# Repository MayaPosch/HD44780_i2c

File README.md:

# HD44780-compatible I2C adapter #

This project is an I2C expander module based around a Texas Instruments TCA6416A I2C GPIO expander. It allows for interfacing with a variety of 14 to 16-pin, HD44780-compatible displays:

- 14-pin without backlight.
- 16-pin with A/K backlight pins after pin 14.
- 16-pin with A/K backlight pins before pin 1.
- 16-pin with Vee negative bias voltage output on pin 16 instead of backlight ground.

This adapter is compatible with both 3.3V and 5V I2C bus levels. The 5-pin MCU/MPU side header has the following connections:

1. **Vlcd:** LCD-side voltage. This is 5V for a 5V display.
2. **GND:** Ground connection.
3. **VDD:** I2C bus voltage. This is 3.3V for a 3.3V MCU.
4. **SDA:** I2C data line. At MCU level voltage.
5. **SCL:** I2C clock line. At MCU level voltage.

## I2C address ##

Default I2C 7-bit address is 0x20, set with JP1 (1-2 connected). To use the alternate 0x21 address, cut the connection on JP1 between pads 1 & 2, and connect 2-3.

## GPIO header ##

Four GPIO pins from the I2C expander are broken out into a 5-pin header (J3). These can be freely used, limited by the TCA6416A's capabilities.

## Vlcd-Vee backlight ##

When a display is connected that does not use pin 16 for Vee (negative bias), but instead expects a 5V backlight supply voltage on this, connect the `Vlcd-Vee` connector with a jumper.

## Backlight enable ##

The backlight on/off state is controlled by GPIO 0 of the TCA6416A via Q1.

## Contrast adjustment ##

For contrast adjustment, a potentiometer on the board is provided.

## TODO ##

This is currently a prototype design. It's likely that some things may not fully work as intended yet.

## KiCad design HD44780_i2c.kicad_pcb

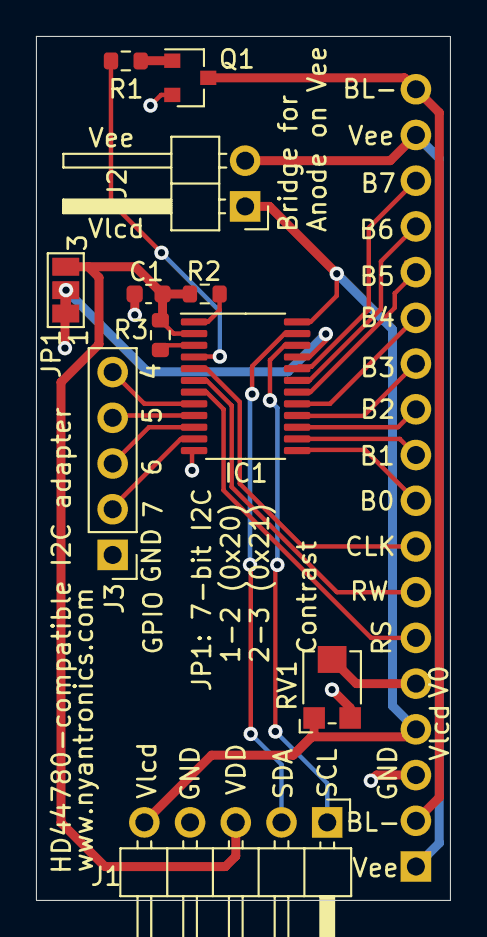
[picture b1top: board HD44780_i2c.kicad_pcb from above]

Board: 2 copper layers, 23.0 x 48.0 mm, 12 parts (1 on the bottom side), 28 nets.

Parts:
C1: 100nF; C_0603_1608Metric
IC1: TCA6416APWR; TSSOP-24_4.4x7.8mm_P0.65mm
J1: Conn_01x05_Male; PinHeader_1x05_P2.54mm_Horizontal
J2: Conn_01x02_Male; PinHeader_1x02_P2.54mm_Horizontal
J3: Conn_01x05; PinHeader_1x05_P2.54mm_Vertical
J4: Conn_01x18_Male; PinHeader_1x18_P2.54mm_Vertical
JP1: SolderJumper_3_Bridged12; SolderJumper-3_P1.3mm_Bridged12_Pad1.0x1.5mm_NumberLabels
Q1: Q_NPN_BCE; SOT-23
R1, R2, R3: 4k7; R_0603_1608Metric
RV1: R_POT_Small; Potentiometer_Bourns_TC33X_Vertical

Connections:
ADDR: IC1.21, JP1.2
B0: IC1.13, J4.9
B1: IC1.14, J4.10
B2: IC1.15, J4.11
B3: IC1.16, J4.12
B4: IC1.17, J4.13
B5: IC1.18, J4.14
B6: IC1.19, J4.15
B7: IC1.20, J4.16
BLK: J4.2, J4.18, Q1.3
BL_TGL: IC1.4, R1.2
CLK: IC1.5, J4.8
GND: C1.2, IC1.12, J1.4, J3.1, J4.3, JP1.1, Q1.2, RV1.3
unnamed: IC1.1, R2.1
unnamed: IC1.3, R3.1
unnamed: IC1.8, J3.5
unnamed: IC1.9, J3.4
unnamed: IC1.10, J3.3
unnamed: IC1.11, J3.2
unnamed: Q1.1, R1.1
RS: IC1.7, J4.6
RW: IC1.6, J4.7
SCL: IC1.22, J1.1
SDA: IC1.23, J1.2
VDD: C1.1, IC1.2, J1.3, JP1.3, R2.2, R3.2
VO: J4.5, RV1.2
Vee: J2.2, J4.1, J4.17
Vlcd: IC1.24, J1.5, J2.1, J4.4, RV1.1

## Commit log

2021-05-10 Initial commit of WIP.
2021-09-12 Replace main IC with Ti version. Reroute PCB. Update silkscreen.
2021-09-12 Add silkscreen docu.
2021-09-12 Update README.
2021-12-12 Correctly orient main header. Update layout & routing.
2021-12-12 Change location of jumper pad. Change Vi2c to VDD.
2021-12-12 Update board render.
2021-12-12 Improve clearance between address pad and components.
2021-12-12 Add HTML BOM file.
2021-12-12 Replace trimmer with most cost-effective variant.
2021-12-12 Add STEP file for trimmer part.
2022-01-07 Update BL cathode naming and schematic comments.
2022-01-07 Update schematic PDF.
